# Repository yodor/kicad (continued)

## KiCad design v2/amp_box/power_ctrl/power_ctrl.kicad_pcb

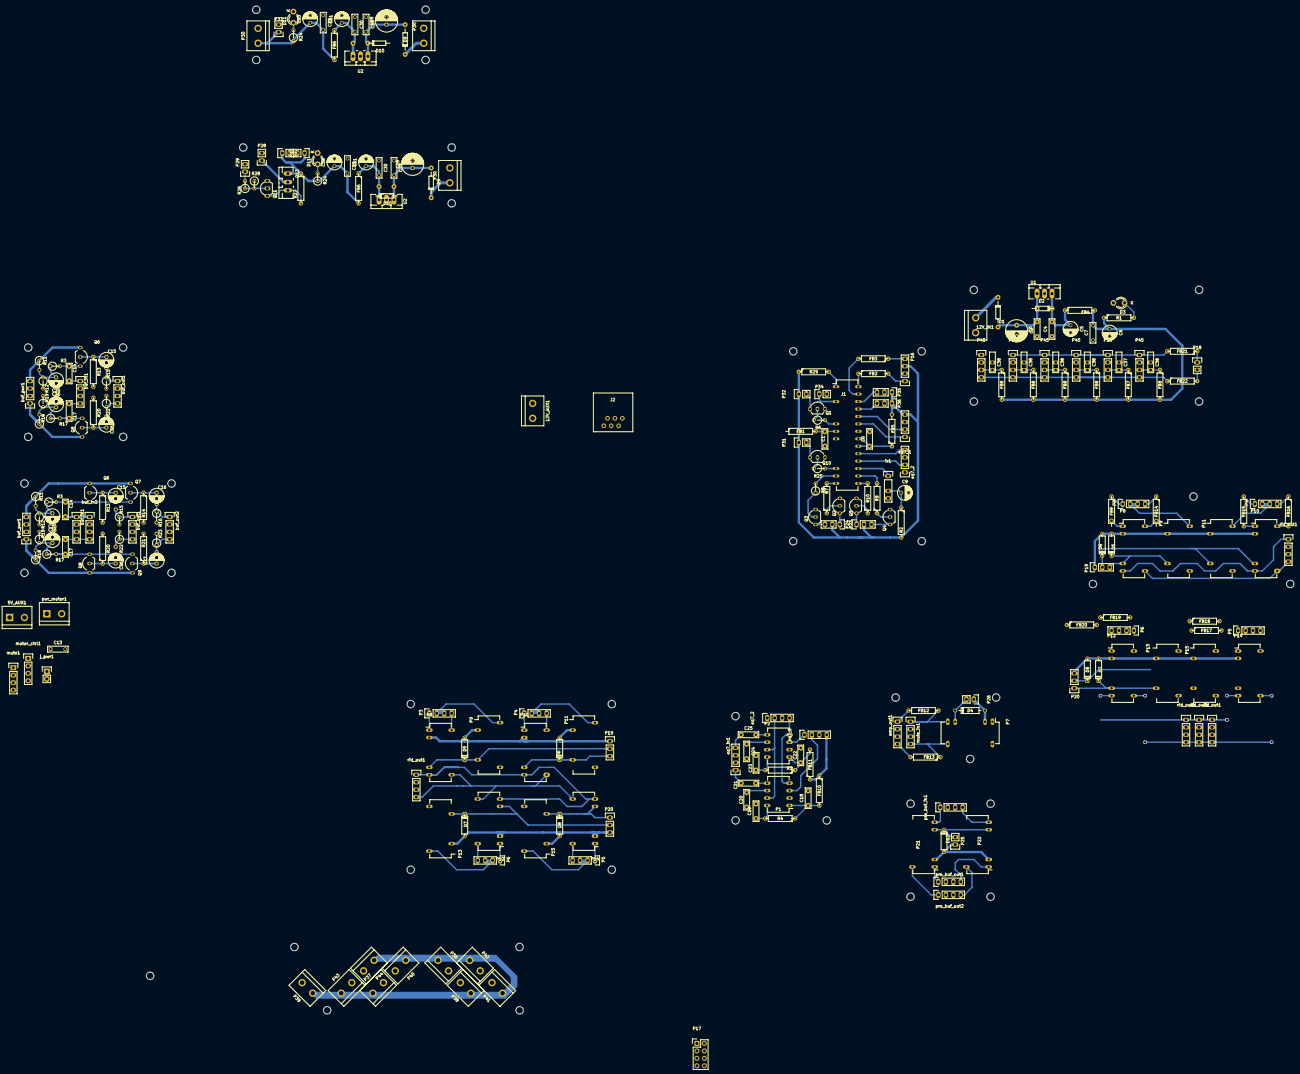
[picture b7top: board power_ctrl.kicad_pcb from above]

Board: 2 copper layers, 434.3 x 343.9 mm, 254 parts (0 on the bottom side), 102 nets.

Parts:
5V_AUX1, 12V_AUX1, 12V_IN1: CONN_2; bornier2
C1, C3, C4, C6, C7, C18, C20, C22, C24, C29, C29#2, C30, C30#2, C32, C32#2, C37, C38, C38#2, C38#3, C38#4, C38#5: 100nF; C_Rect_L7_W2_P5
C2, C28, C28#2: 470uF; C_Radial_D7.5_L11.2_P2.5
C5, C8, C31, C31#2, C33, C33#2: 10uF; C_Radial_D5_L6_P2.5
C9: 4.7uF; C_Radial_D5_L11_P2.5
C13: 470uF; C_Rect_L7_W2_P5
C14, C14#2, C17, C17#2: 0.1; C_Rect_L7_W2_P5
C15, C15#2, C16, C26, C26#2, C27: 4.7uF; C_Radial_D5_L11_P2
C19, C23: 33pF; C_Rect_L7_W2_P5
C21, C25: 1uF; C_Rect_L7_W2_P5
C35, C35#2, C36, C36#2: 10uF; C_Radial_D5_L11_P2
D1, D2, D9, D9#2, D10, D10#2: DIODE; Diode_DO-35_SOD27_Horizontal_RM10
D3, D11, D11#2: LED; LED-3MM
D4, D5, D5#2, D6, D6#2, D7, D7#2, D8, D8#2, D12: DIODE; D3
FB1, FB2, FB3, FB4, FB5, FB6, FB6#2, FB7, FB8, FB8#2, FB8#3, FB8#4, FB8#5, FB9, FB10, FB11, FB12, FB13, FB14, FB15, FB16, FB17, FB18, FB19, FB20, FB21, FB22: FILTER; R4
J1: Atmega328; DIP-28_W7.62mm_LongPads
J2: RJ12; RJ12_E
P1, P2: Msgeq7_1; DIP-8_W7.62mm_LongPads
P3, P3#2, P4, P4#2, P5, P5#2, P6, P6#2, P16, P16#2, P45, P45#2, P45#3, P45#4, P45#5: CONN_4; Pin_Header_Straight_1x04
P7, P8, P8#2, P10, P10#2, P12, P12#2, P14, P14#2, P21, P22: DIP05-2A72-21L; DIP-14_W7.62mm_LongPads
P9, P9#2, P11, P11#2, P13, P13#2, P15, P15#2: DIP05-1A72-12L; DIP-14_W7.62mm_LongPads
P17: CONN_02X04; Pin_Header_Straight_2x04
P18, P25, P26, P27, P28, P29, P31, P32, P33, P33#2, P34: CONN_01X02; Pin_Header_Straight_1x02
P19, P19#2, P20, P20#2, P23, P24, P35, P36: CONN_01X03; Pin_Header_Straight_1x03
P30, P30#2, P30#3: CONN_01X02; bornier2
P37, P38, P38#2, P39, P40, P41, P42, P43, P44: CONN_2; bornier2
Q1, Q2, Q3, Q4, Q5, Q10, Q11: BC547; TO-92_Inline_Wide
Q6, Q6#2, Q7, Q8, Q8#2, Q9: Q_NJFET_DSG; TO-92_Inline_Wide
Q12: Q_PMOS_GDS; TO-220_Neutral123_Vertical_LargePads
R1: 680R; R4
R2: 100R; R4
R3, R3#2, R17, R17#2: 10M; R1
R4, R5: 200K; R4
R6, R8, R25: 12K; R1
R7, R9, R10: 12K; R4
R11, R11#2, R12, R12#2, R18, R18#2, R19, R19#2: 2.2M; R1
R13, R13#2, R14, R20, R20#2, R21: 3K; R4
R15, R15#2, R16, R22, R22#2, R23: 100K; R1
R24, R24#2: 680R; R1
R26, R28: 10K; R1
R27, R29: 10K; R4
U1: 7805; TO-220_Neutral123_Vertical_LargePads
U2, U2#2: 7809; TO-220_Neutral123_Vertical_LargePads
amp_out1: CONN_4; Pin_Header_Straight_1x04
buf_in1, buf_in1#2, buf_in2: CONN_4; Pin_Header_Straight_1x04
buf_out1, buf_out1#2, buf_out2: CONN_4; Pin_Header_Straight_1x04
buf_pwr1, buf_pwr1#2: CONN_4; Pin_Header_Straight_1x04
eq7_1, eq7_1#2, eq7_2, eq7_2#2, eq7_in1: CONN_4; Pin_Header_Straight_1x04
ir1: CONN_4; Pin_Header_Straight_1x04
j_pwr1: CONN_2; Pin_Header_Straight_1x02
motor_ctrl1: CONN_4; Pin_Header_Straight_1x04
mute1: CONN_01X04; Pin_Header_Straight_1x04
mute_in1: CONN_4; Pin_Header_Straight_1x04
pre_buf_in1: CONN_4; Pin_Header_Straight_1x04
pre_buf_out1, pre_buf_out2: CONN_4; Pin_Header_Straight_1x04
pwr_motor1: CONN_2; bornier2
rid_out1, rid_out1#2, rid_out1#3, rid_out1#4, rid_out1#5: CONN_4; Pin_Header_Straight_1x04

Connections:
+9V: C32.2, C32#2.2, C33.1, C33#2.1, FB6.2, FB6#2.2, P27.1, P33.1, P33#2.1, Q6.1, Q6#2.1, Q7.1, Q8.1, Q8#2.1, Q9.1, Q12.3, R11.1, R11#2.1, R18.1, R18#2.1, R24.1, R24#2.1, R27.1, buf_pwr1.1, buf_pwr1.4, buf_pwr1#2.1, buf_pwr1#2.4
/5V: 5V_AUX1.1, C7.2, C8.1, D4.2, D5.2, D5#2.2, D6.2, D6#2.2, D7.2, D7#2.2, D8.2, D8#2.2, D12.2, FB1.1, FB4.2, FB5.2, FB7.2, FB8.2, FB8#2.2, FB8#3.2, FB8#4.2, FB8#5.2, FB10.1, FB11.1, P7.2, P8.2, P8#2.2, P9.2, P9#2.2, P10.2, P10#2.2, P11.2, P11#2.2, P12.2, P12#2.2, P13.2, P13#2.2, P14.2, P14#2.2, P15.2, P15#2.2, P16#2.3, P19.1, P19#2.1, P20.3, P20#2.3, P21.2, P22.2, P23.2, P24.2, P25.1, P26.1, P31.1, P32.1, P35.1, P36.1, R1.1, R2.2, R29.1, eq7_1.4, eq7_1#2.4, j_pwr1.1, mute1.1
/9V_SW: P28.1, Q12.2
/12V: 12V_AUX1.1, 12V_IN1.1, D1.1, D9.1, D9#2.1, P30#2.1, P30#3.1, P37.1, P38.1, P38#2.1, P39.1, P40.1, P41.1, P42.1, P43.1, P44.1
/CH1: J1.14, R7.2
/CH1_EN: D5.1, D5#2.1, P8.6, P8#2.6, P9.6, P9#2.6, P19.3, P19#2.2, P23.1, Q2.1
/CH2: J1.13, R8.2
/CH2_EN: D6.1, D6#2.1, P10.6, P10#2.6, P11.6, P11#2.6, P19.2, P19#2.3, P23.3, Q3.1
/CH3: J1.15, R10.2
/CH3_EN: D8.1, D8#2.1, P14.6, P14#2.6, P15.6, P15#2.6, P20.2, P20#2.1, P24.1, Q5.1
/CH4: J1.16, R9.2
/CH4_EN: D7.1, D7#2.1, P12.6, P12#2.6, P13.6, P13#2.6, P20.1, P20#2.2, P24.3, Q4.1
/EQ7_DATA_L: J1.24, P1.3, P17.6, eq7_1.2, eq7_1#2.2
/EQ7_DATA_R: J1.23, P2.3, P17.8, eq7_1.1, eq7_1#2.1
/EQ7_RST: J1.18, P1.7, P2.7, P17.3, eq7_2.2, eq7_2#2.2
/EQ7_STROBE: J1.19, P1.4, P2.4, P17.7, eq7_2.4, eq7_2#2.4
/G_IN1: P3.2, P3.3, P3#2.2, P3#2.3, P9.14, P9#2.14
/G_IN2: P4.2, P4.3, P4#2.2, P4#2.3, P11.14, P11#2.14
/G_IN3: P5.2, P5.3, P5#2.2, P5#2.3, P15.14, P15#2.14
/G_IN4: P6.2, P6.3, P6#2.2, P6#2.3, P13.14, P13#2.14
/IR_IN: J1.17, ir1.1
/L_IN1: FB9.2, P3#2.1, P8.1, P8#2.1
/L_IN2: FB15.2, P4#2.1, P10.1, P10#2.1
/L_IN3: FB17.2, P5#2.1, P14.1, P14#2.1
/L_IN4: FB19.2, P6#2.1, P12.1, P12#2.1
/L_OUT: P8.7, P8#2.7, P10.7, P10#2.7, P12.7, P12#2.7, P14.7, P14#2.7, P21.7, pre_buf_in1.1, rid_out1.1, rid_out1#2.1, rid_out1#3.1, rid_out1#4.1, rid_out1#5.1
/L_OUT_BUF: C14.2, C14#2.2, P21.1, buf_in1.1, buf_in1#2.1, buf_in2.1, pre_buf_out1.1
/L_OUT_BUF1: C15.2, C15#2.2, C21.1, R15.1, R15#2.1, buf_out1.1, buf_out1#2.1, eq7_in1.1
/L_OUT_BUF2: C16.2, FB12.1, P7.7, R16.1, buf_out2.1, mute_in1.1
/L_OUT_PRE: P21.14, pre_buf_out2.1
/MUTE: J1.6, R6.2
/MUTE_EN: D4.1, P7.6, P26.2, P32.2, Q1.1
/PREAMP: J1.12, R25.2
/PREAMP_EN: D12.1, P21.6, P22.6, P25.2, P31.2, Q10.1
/PREAMP_PWR_EN: J1.3, P34.1
/P_PWR_EN: P29.1, R26.2
/R_IN1: FB14.2, P3#2.4, P8.14, P8#2.14
/R_IN2: FB16.2, P4#2.4, P10.14, P10#2.14
/R_IN3: FB18.2, P5#2.4, P14.14, P14#2.14
/R_IN4: FB20.2, P6#2.4, P12.14, P12#2.14
/R_OUT: P8.8, P8#2.8, P10.8, P10#2.8, P12.8, P12#2.8, P14.8, P14#2.8, P22.7, pre_buf_in1.4, rid_out1.4, rid_out1#2.4, rid_out1#3.4, rid_out1#4.4, rid_out1#5.4
/R_OUT_BUF: C17.2, C17#2.2, P22.1, buf_in1.4, buf_in1#2.4, buf_in2.4, pre_buf_out1.4
/R_OUT_BUF1: C25.1, C26.2, C26#2.2, R22.1, R22#2.1, buf_out1.4, buf_out1#2.4, eq7_in1.4
/R_OUT_BUF2: C27.2, FB13.1, P7.8, R23.1, buf_out2.4, mute_in1.4
/R_OUT_PRE: P22.14, pre_buf_out2.4
/SCL: FB2.2, FB21.2, P16.1, P16#2.1, P45.1, P45#2.1, P45#3.1, P45#4.1, P45#5.1
/SCL_OUT: FB21.1, J2.2, P18.1
/SDA: FB3.1, FB22.1, P16.4, P16#2.4, P45.4, P45#2.4, P45#3.4, P45#4.4, P45#5.4
/SDA_OUT: FB22.2, J2.5, P18.2
/SPK_MUTE_EN: mute1.3, mute1.4
/TEMP_L: J1.25, P36.3
/TEMP_R: J1.26, P35.3
/VBIAS_L: C35.1, C35#2.1, R3.1, R3#2.1, R11.2, R11#2.2, R12.1, R12#2.1
/VBIAS_R: C36.1, C36#2.1, R17.1, R17#2.1, R18.2, R18#2.2, R19.1, R19#2.1
/VIN_MOTOR: C13.1, j_pwr1.2, pwr_motor1.2
GND: 5V_AUX1.2, 12V_AUX1.2, 12V_IN1.2, C1.1, C2.2, C3.1, C4.1, C5.2, C6.2, C7.1, C8.2, C9.2, C13.2, C18.2, C19.2, C20.2, C22.2, C23.2, C24.2, C28.2, C28#2.2, C29.1, C29#2.1, C30.1, C30#2.1, C31.2, C31#2.2, C32.1, C32#2.1, C33.2, C33#2.2, C35.2, C35#2.2, C36.2, C36#2.2, C37.1, C38.1, C38#2.1, C38#3.1, C38#4.1, C38#5.1, D3.1, D11.1, D11#2.1, J1.8, J1.22, J2.1, J2.3, J2.4, J2.6, P1.2, P2.2, P7.1, P7.14, P9.8, P9#2.8, P11.8, P11#2.8, P13.8, P13#2.8, P15.8, P15#2.8, P16.2, P16#2.2, P17.1, P17.4, P17.5, P27.2, P28.2, P29.2, P30.2, P30#2.2, P30#3.2, P33.2, P33#2.2, P34.2, P35.2, P36.2, P37.2, P38.2, P38#2.2, P39.2, P40.2, P41.2, P42.2, P43.2, P44.2, P45.2, P45#2.2, P45#3.2, P45#4.2, P45#5.2, Q1.3, Q2.3, Q3.3, Q4.3, Q5.3, Q10.3, Q11.3, R12.2, R12#2.2, R13.2, R13#2.2, R14.2, R15.2, R15#2.2, R16.2, R19.2, R19#2.2, R20.2, R20#2.2, R21.2, R22.2, R22#2.2, R23.2, R28.1, U1.GND, U2.GND, U2#2.GND, amp_out1.2, amp_out1.3, buf_in1.2, buf_in1.3, buf_in1#2.2, buf_in1#2.3, buf_in2.2, buf_in2.3, buf_out1.2, buf_out1.3, buf_out1#2.2, buf_out1#2.3, buf_out2.2, buf_out2.3, buf_pwr1.2, buf_pwr1.3, buf_pwr1#2.2, buf_pwr1#2.3, eq7_1.3, eq7_1#2.3, eq7_2.1, eq7_2.3, eq7_2#2.1, eq7_2#2.3, eq7_in1.2, eq7_in1.3, ir1.4, motor_ctrl1.2, motor_ctrl1.3, mute1.2, mute_in1.2, mute_in1.3, pre_buf_in1.2, pre_buf_in1.3, pre_buf_out1.2, pre_buf_out1.3, pre_buf_out2.2, pre_buf_out2.3, pwr_motor1.1, rid_out1.2, rid_out1.3, rid_out1#2.2, rid_out1#2.3, rid_out1#3.2, rid_out1#3.3, rid_out1#4.2, rid_out1#4.3, rid_out1#5.2, rid_out1#5.3
unnamed: C1.2, FB1.2, J1.7
unnamed: C2.1, C3.2, D1.2, D2.2, U1.VI
unnamed: C4.2, C5.1, D2.1, FB4.1, U1.VO
unnamed: C6.1, FB5.1, J1.20, J1.21, P17.2
unnamed: C9.1, R2.1, ir1.3
unnamed: C14.1, C14#2.1, Q6.3, Q6#2.3, Q7.3, R3.2, R3#2.2
unnamed: C15.1, C15#2.1, Q6.2, Q6#2.2, R13.1, R13#2.1
unnamed: C16.1, Q7.2, R14.1
unnamed: C17.1, C17#2.1, Q8.3, Q8#2.3, Q9.3, R17.2, R17#2.2
unnamed: C18.1, FB10.2, P1.1, R4.1
unnamed: C19.1, P1.8, R4.2
unnamed: C20.1, P1.6
unnamed: C21.2, P1.5
unnamed: C22.1, FB11.2, P2.1, R5.1
unnamed: C23.1, P2.8, R5.2
unnamed: C24.1, P2.6
unnamed: C25.2, P2.5
unnamed: C26.1, C26#2.1, Q8.2, Q8#2.2, R20.1, R20#2.1
unnamed: C27.1, Q9.2, R21.1
unnamed: C28.1, C28#2.1, C29.2, C29#2.2, D9.2, D9#2.2, D10.2, D10#2.2, U2.VI, U2#2.VI
unnamed: C30.2, C30#2.2, C31.1, C31#2.1, D10.1, D10#2.1, FB6.1, FB6#2.1, U2.VO, U2#2.VO
unnamed: C37.2, FB7.1, P16.3
unnamed: C38.2, C38#2.2, C38#3.2, C38#4.2, C38#5.2, FB8.1, FB8#2.1, FB8#3.1, FB8#4.1, FB8#5.1, P45.3, P45#2.3, P45#3.3, P45#4.3, P45#5.3
unnamed: D3.2, R1.2
unnamed: D11.2, D11#2.2, R24.2, R24#2.2
unnamed: FB2.1, J1.28
unnamed: FB3.2, J1.27
unnamed: FB9.1, P3.1
unnamed: FB12.2, amp_out1.1
unnamed: FB13.2, amp_out1.4
unnamed: FB14.1, P3.4
unnamed: FB15.1, P4.1
unnamed: FB16.1, P4.4
unnamed: FB17.1, P5.1
unnamed: FB18.1, P5.4
unnamed: FB19.1, P6.1
unnamed: FB20.1, P6.4
unnamed: J1.1, R29.2
unnamed: Q1.2, R6.1
unnamed: Q2.2, R7.1
unnamed: Q3.2, R8.1
unnamed: Q4.2, R9.1
unnamed: Q5.2, R10.1
unnamed: Q10.2, R25.1
unnamed: Q11.1, Q12.1, R27.2
unnamed: Q11.2, R26.1, R28.2

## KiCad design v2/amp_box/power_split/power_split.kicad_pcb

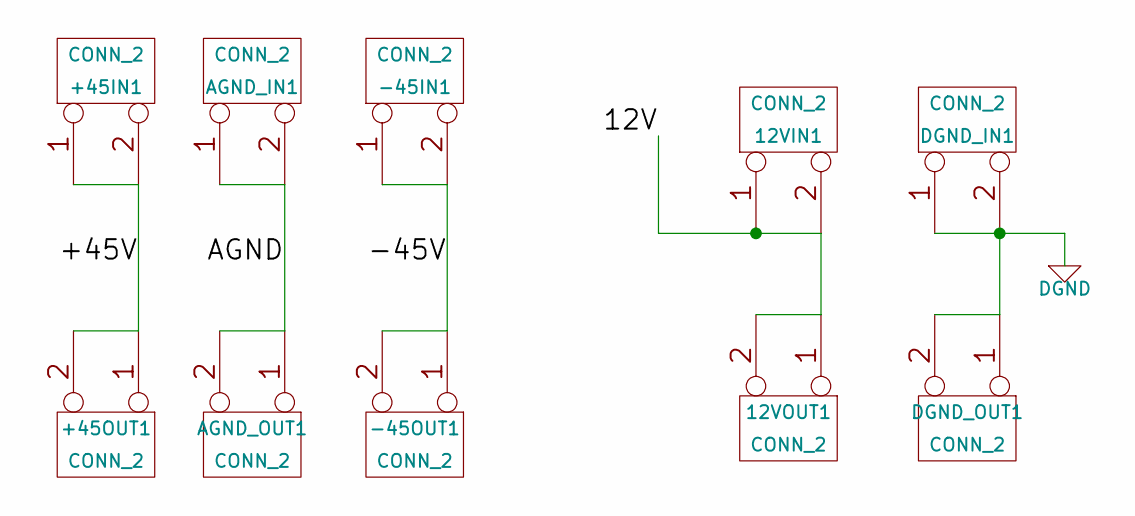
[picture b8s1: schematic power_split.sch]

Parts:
12VIN1, 12VOUT1: CONN_2
+45IN1, +45OUT1: CONN_2
-45IN1, -45OUT1: CONN_2
AGND_IN1: CONN_2
AGND_OUT1: CONN_2
DGND_IN1: CONN_2
DGND_OUT1: CONN_2

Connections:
/12V: 12VIN1.1, 12VIN1.2 (PM), 12VOUT1.1, 12VOUT1.2 (PM)
/+45V: +45IN1.1, +45IN1.2 (PM), +45OUT1.1, +45OUT1.2 (PM)
/-45V: -45IN1.1, -45IN1.2 (PM), -45OUT1.1, -45OUT1.2 (PM)
/AGND: AGND_IN1.1, AGND_IN1.2 (PM), AGND_OUT1.1, AGND_OUT1.2 (PM)
DGND: DGND_IN1.1, DGND_IN1.2 (PM), DGND_OUT1.1, DGND_OUT1.2 (PM)

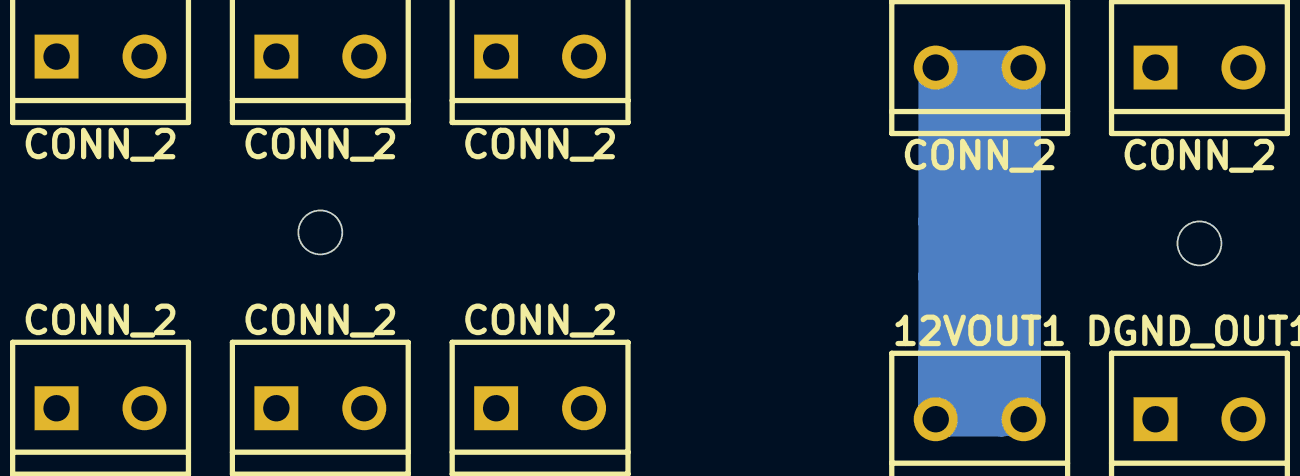
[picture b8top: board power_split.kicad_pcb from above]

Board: 2 copper layers, 10 parts (0 on the bottom side), 5 nets.
